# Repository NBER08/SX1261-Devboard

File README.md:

#SX1261 devboard for LoRa testing

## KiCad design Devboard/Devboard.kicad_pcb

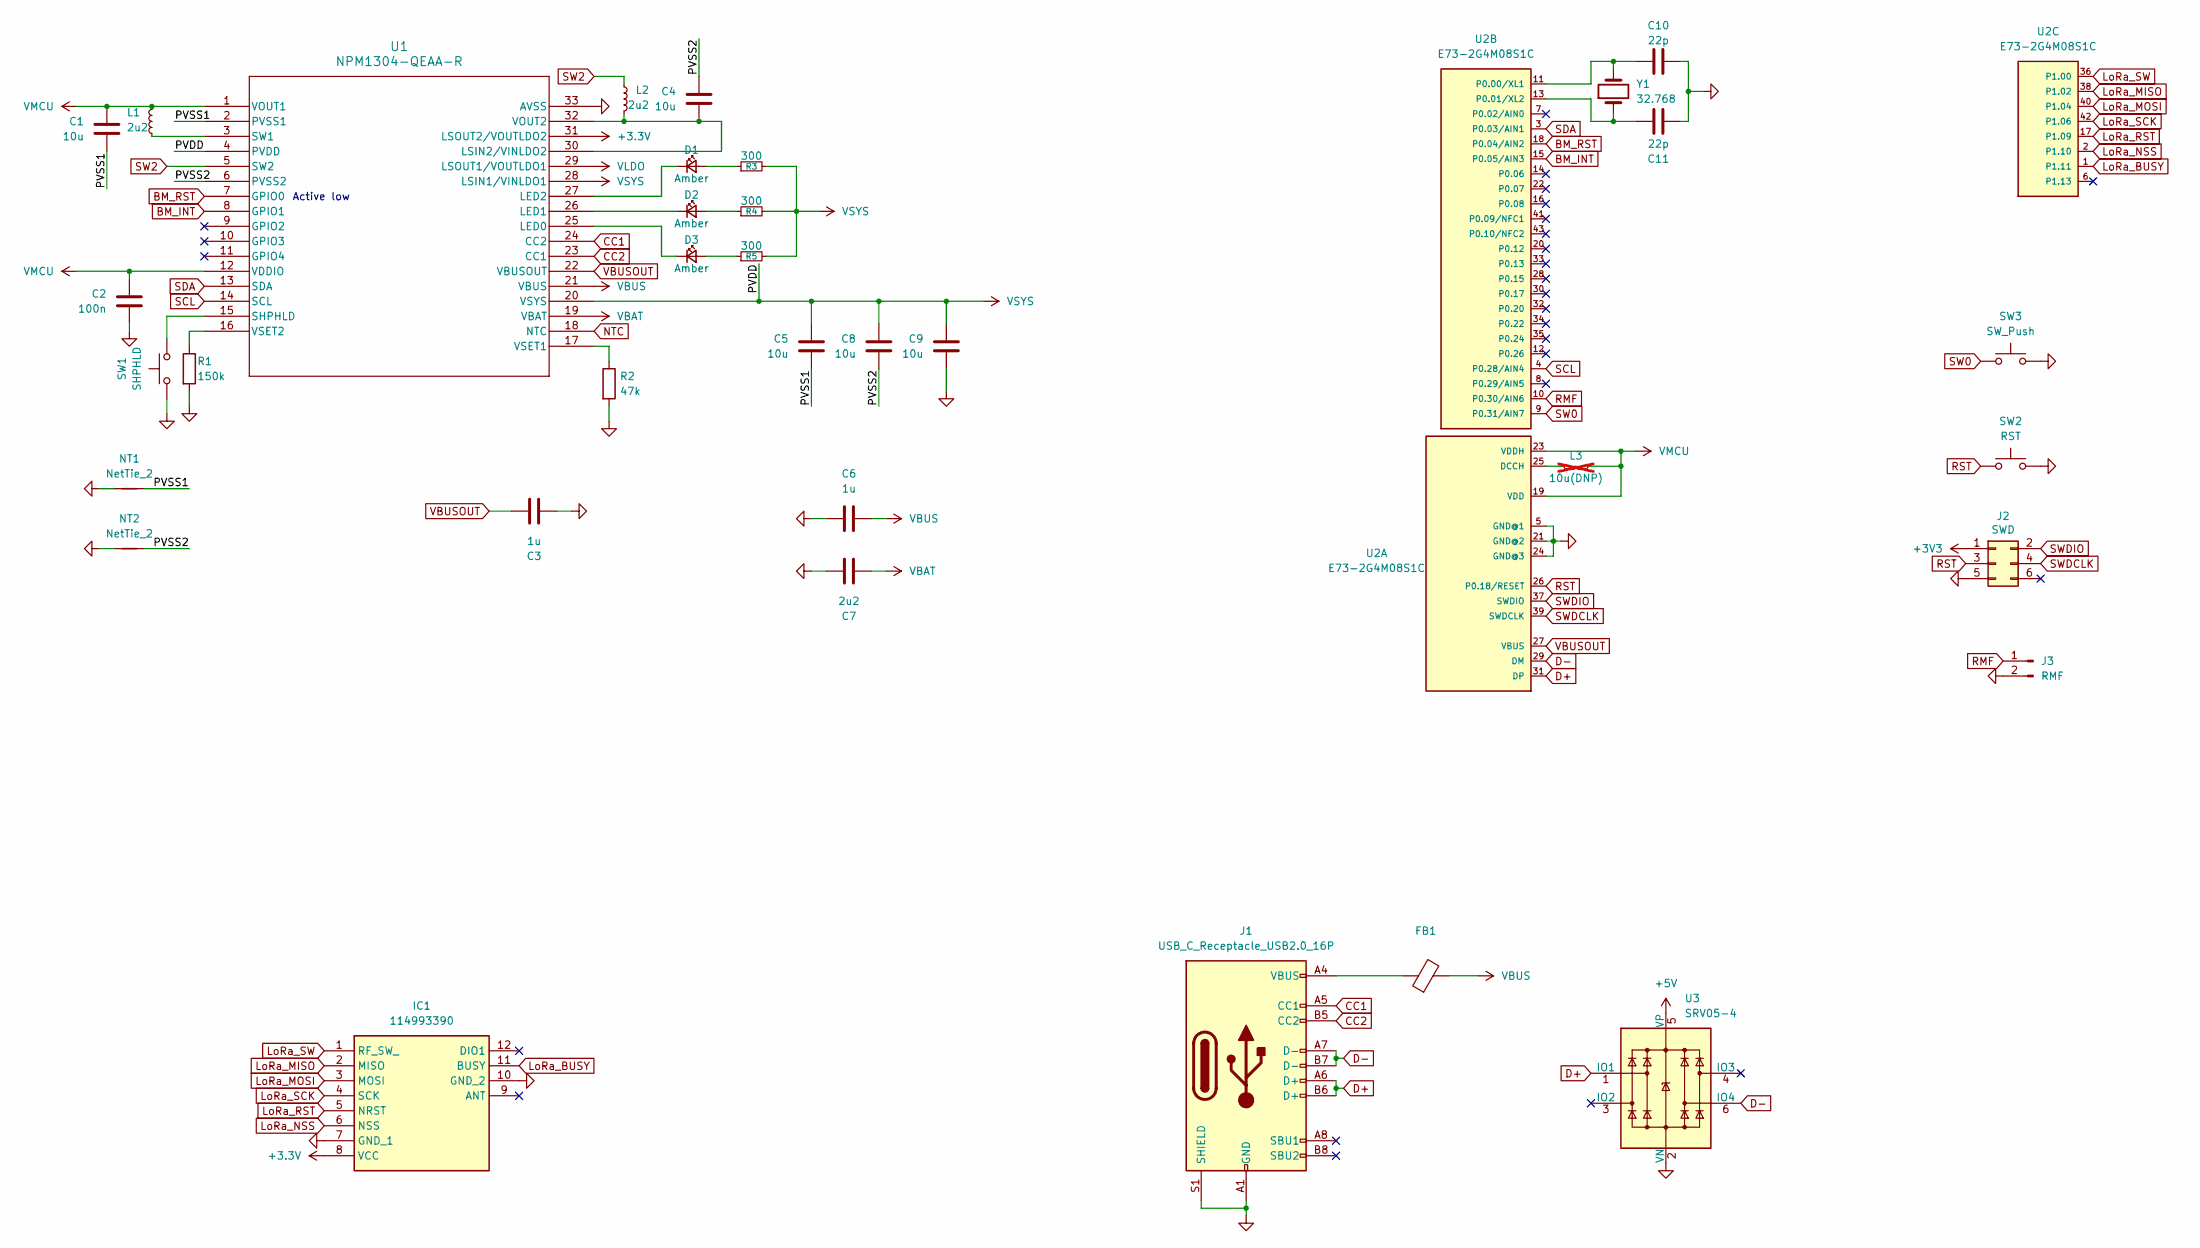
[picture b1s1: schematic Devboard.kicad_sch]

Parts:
C1, C4, C5, C8, C9: 10u; C_1206_3216Metric_Pad1.33x1.80mm_HandSolder
C2: 100n; C_1206_3216Metric_Pad1.33x1.80mm_HandSolder
C3, C6: 1u; C_1206_3216Metric_Pad1.33x1.80mm_HandSolder
C7: 2u2; C_1206_3216Metric_Pad1.33x1.80mm_HandSolder
C10, C11: 22p; C_1206_3216Metric_Pad1.33x1.80mm_HandSolder
D1, D2, D3: Amber; LED_1206_3216Metric_Pad1.42x1.75mm_HandSolder
FB1: LI0603G121R-10; L_1206_3216Metric_Pad1.22x1.90mm_HandSolder
IC1: 114993390; Mouser Part Number 713-114993390
J1: USB_C_Receptacle_USB2.0_16P; USB_C_Receptacle_GCT_USB4105-xx-A_16P_TopMnt_Horizontal
J2: SWD; PinHeader_2x03_P2.54mm_Vertical
J3: RMF; PinHeader_1x02_P2.54mm_Vertical
L1, L2: 2u2; L_0805_2012Metric_Pad1.05x1.20mm_HandSolder
L3: 10u(DNP); L_Changjiang_FTC201610D; not fitted
NT1, NT2: NetTie_2; NetTie-2_SMD_Pad0.5mm
R1: 150k; R_1206_3216Metric_Pad1.30x1.75mm_HandSolder
R2: 47k; R_1206_3216Metric_Pad1.30x1.75mm_HandSolder
R3, R4, R5: 300; R_1206_3216Metric_Pad1.30x1.75mm_HandSolder
SW1: SHPHLD; SW_Push_1P1T_NO_CK_KMR2
SW2: RST; SW_Push_1P1T_NO_CK_KMR2
SW3: SW_Push; SW_Push_1P1T_NO_CK_KMR2
U1: NPM1304-QEAA-R; QFN32_5X5_NOR
U2: E73-2G4M08S1C
U3: SRV05-4; SOT-23-6_Handsoldering
Y1: 32.768; Crystal_SMD_MicroCrystal_CC1V-T1A-2Pin_8.0x3.7mm

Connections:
+3.3V: IC1.8 (VCC), U1.31 (LSOUT2/VOUTLDO2)
+3V3: J2.1
+5V: U3.5 (VP)
/PVSS1: C1.1, C5.1, NT1.2, U1.2 (PVSS1)
/PVSS2: C4.2, C8.1, NT2.2, U1.6 (PVSS2)
BM_INT: U1.8 (GPIO1), U2.15 (P0.05/AIN3)
BM_RST: U1.7 (GPIO0), U2.18 (P0.04/AIN2)
CC1: J1.A5 (CC1), U1.24 (CC2)
CC2: J1.B5 (CC2), U1.23 (CC1)
D+: J1.A6 (D+), J1.B6 (D+), U2.31 (DP), U3.1 (IO1)
D-: J1.A7 (D-), J1.B7 (D-), U2.29 (DM), U3.6 (IO4)
GND: C2.2, C3.1, C6.1, C7.1, C9.1, C10.1, C11.1, IC1.7 (GND_1), IC1.10 (GND_2), J1.A1 (GND), J1.A12 (GND), J1.B1 (GND), J1.B12 (GND), J1.S1 (SHIELD), J1.SH, J2.5, J3.2, NT1.1, NT2.1, R1.2, R2.2, SW1.2, SW2.2, SW3.2, U1.33 (AVSS), U2.5 (GND@1), U2.21 (GND@2), U2.24 (GND@3), U3.2 (VN)
LoRa_BUSY: IC1.11 (BUSY), U2.1 (P1.11)
LoRa_MISO: IC1.2 (MISO), U2.38 (P1.02)
LoRa_MOSI: IC1.3 (MOSI), U2.40 (P1.04)
LoRa_NSS: IC1.6 (NSS), U2.2 (P1.10)
LoRa_RST: IC1.5 (NRST), U2.17 (P1.09)
LoRa_SCK: IC1.4 (SCK), U2.42 (P1.06)
LoRa_SW: IC1.1 (RF_SW_), U2.36 (P1.00)
NTC: U1.18 (NTC)
unnamed: D1.2 (A), R3.1
unnamed: D1.1 (K), U1.27 (LED2)
unnamed: D2.2 (A), R4.1
unnamed: D2.1 (K), U1.26 (LED1)
unnamed: D3.2 (A), R5.1
unnamed: D3.1 (K), U1.25 (LED0)
unnamed: FB1.1, J1.A4 (VBUS), J1.A9 (VBUS), J1.B4 (VBUS), J1.B9 (VBUS)
unnamed: C4.1, L2.1, U1.30 (LSIN2/VINLDO2), U1.32 (VOUT2)
unnamed: SW1.1, U1.15 (SHPHLD)
unnamed: L1.1, U1.3 (SW1)
unnamed: R2.1, U1.17 (VSET1)
unnamed: R1.1, U1.16 (VSET2)
unnamed: L3.1, U2.25 (DCCH)
unnamed: C10.2, U2.11 (P0.00/XL1), Y1.2
unnamed: C11.2, U2.13 (P0.01/XL2), Y1.1
RMF: J3.1, U2.10 (P0.30/AIN6)
RST: J2.3, SW2.1, U2.26 (P0.18/RESET)
SCL: U1.14 (SCL), U2.4 (P0.28/AIN4)
SDA: U1.13 (SDA), U2.3 (P0.03/AIN1)
SW0: SW3.1, U2.9 (P0.31/AIN7)
SW2: L2.2, U1.5 (SW2)
SWDCLK: J2.4, U2.39 (SWDCLK)
SWDIO: J2.2, U2.37 (SWDIO)
VBAT: C7.2, U1.19 (VBAT)
VBUS: C6.2, FB1.2, U1.21 (VBUS)
VBUSOUT: C3.2, U1.22 (VBUSOUT), U2.27 (VBUS)
VLDO: U1.29 (LSOUT1/VOUTLDO1)
VMCU: C1.2, C2.1, L1.2, L3.2, U1.1 (VOUT1), U1.12 (VDDIO), U2.19 (VDD), U2.23 (VDDH)
VSYS: C5.2, C8.2, C9.2, R3.2, R4.2, R5.2, U1.4 (PVDD), U1.20 (VSYS), U1.28 (LSIN1/VINLDO1)

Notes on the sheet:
Active low

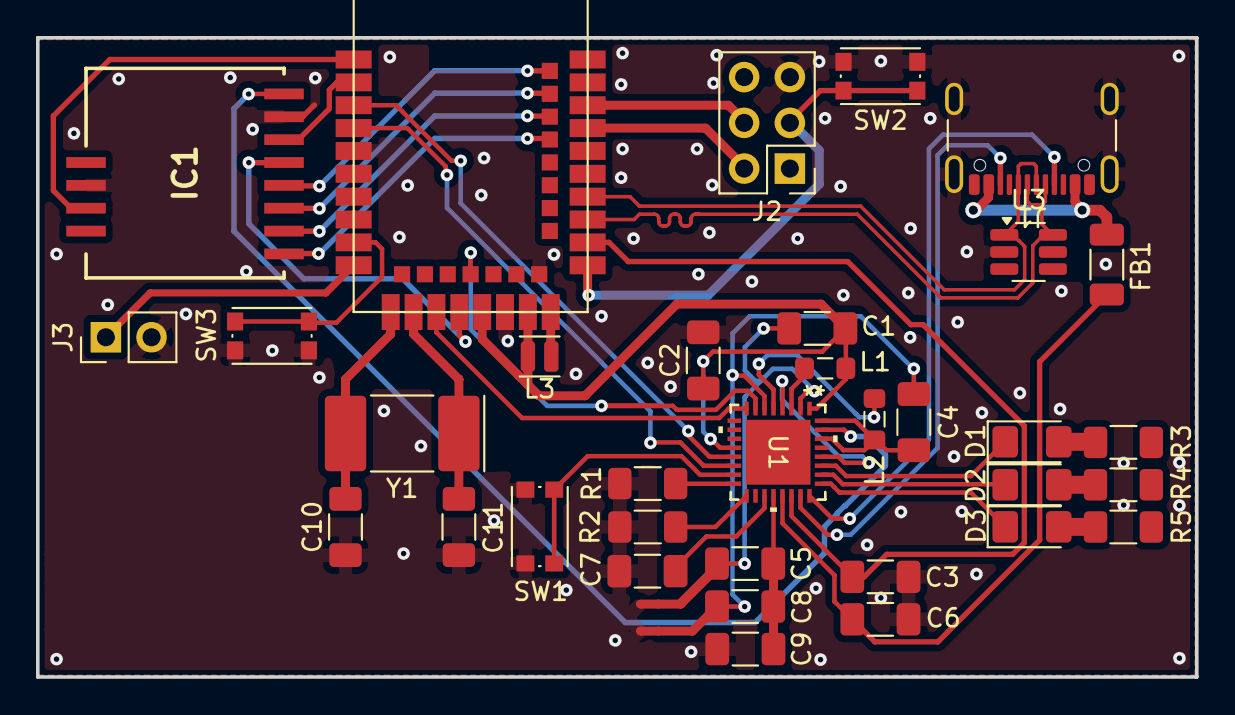
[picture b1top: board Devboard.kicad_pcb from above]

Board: 2 copper layers, 64.4 x 35.5 mm, 36 parts (0 on the bottom side), 45 nets.

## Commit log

2026-05-22 Added README
2026-05-22 Add CERN Open Hardware Licence Version 2
    Added CERN Open Hardware Licence Version 2 - Strongly Reciprocal to the project.
2026-05-22 started schematic design
2026-05-28 Continued design
2026-05-30 Finished design and layout
